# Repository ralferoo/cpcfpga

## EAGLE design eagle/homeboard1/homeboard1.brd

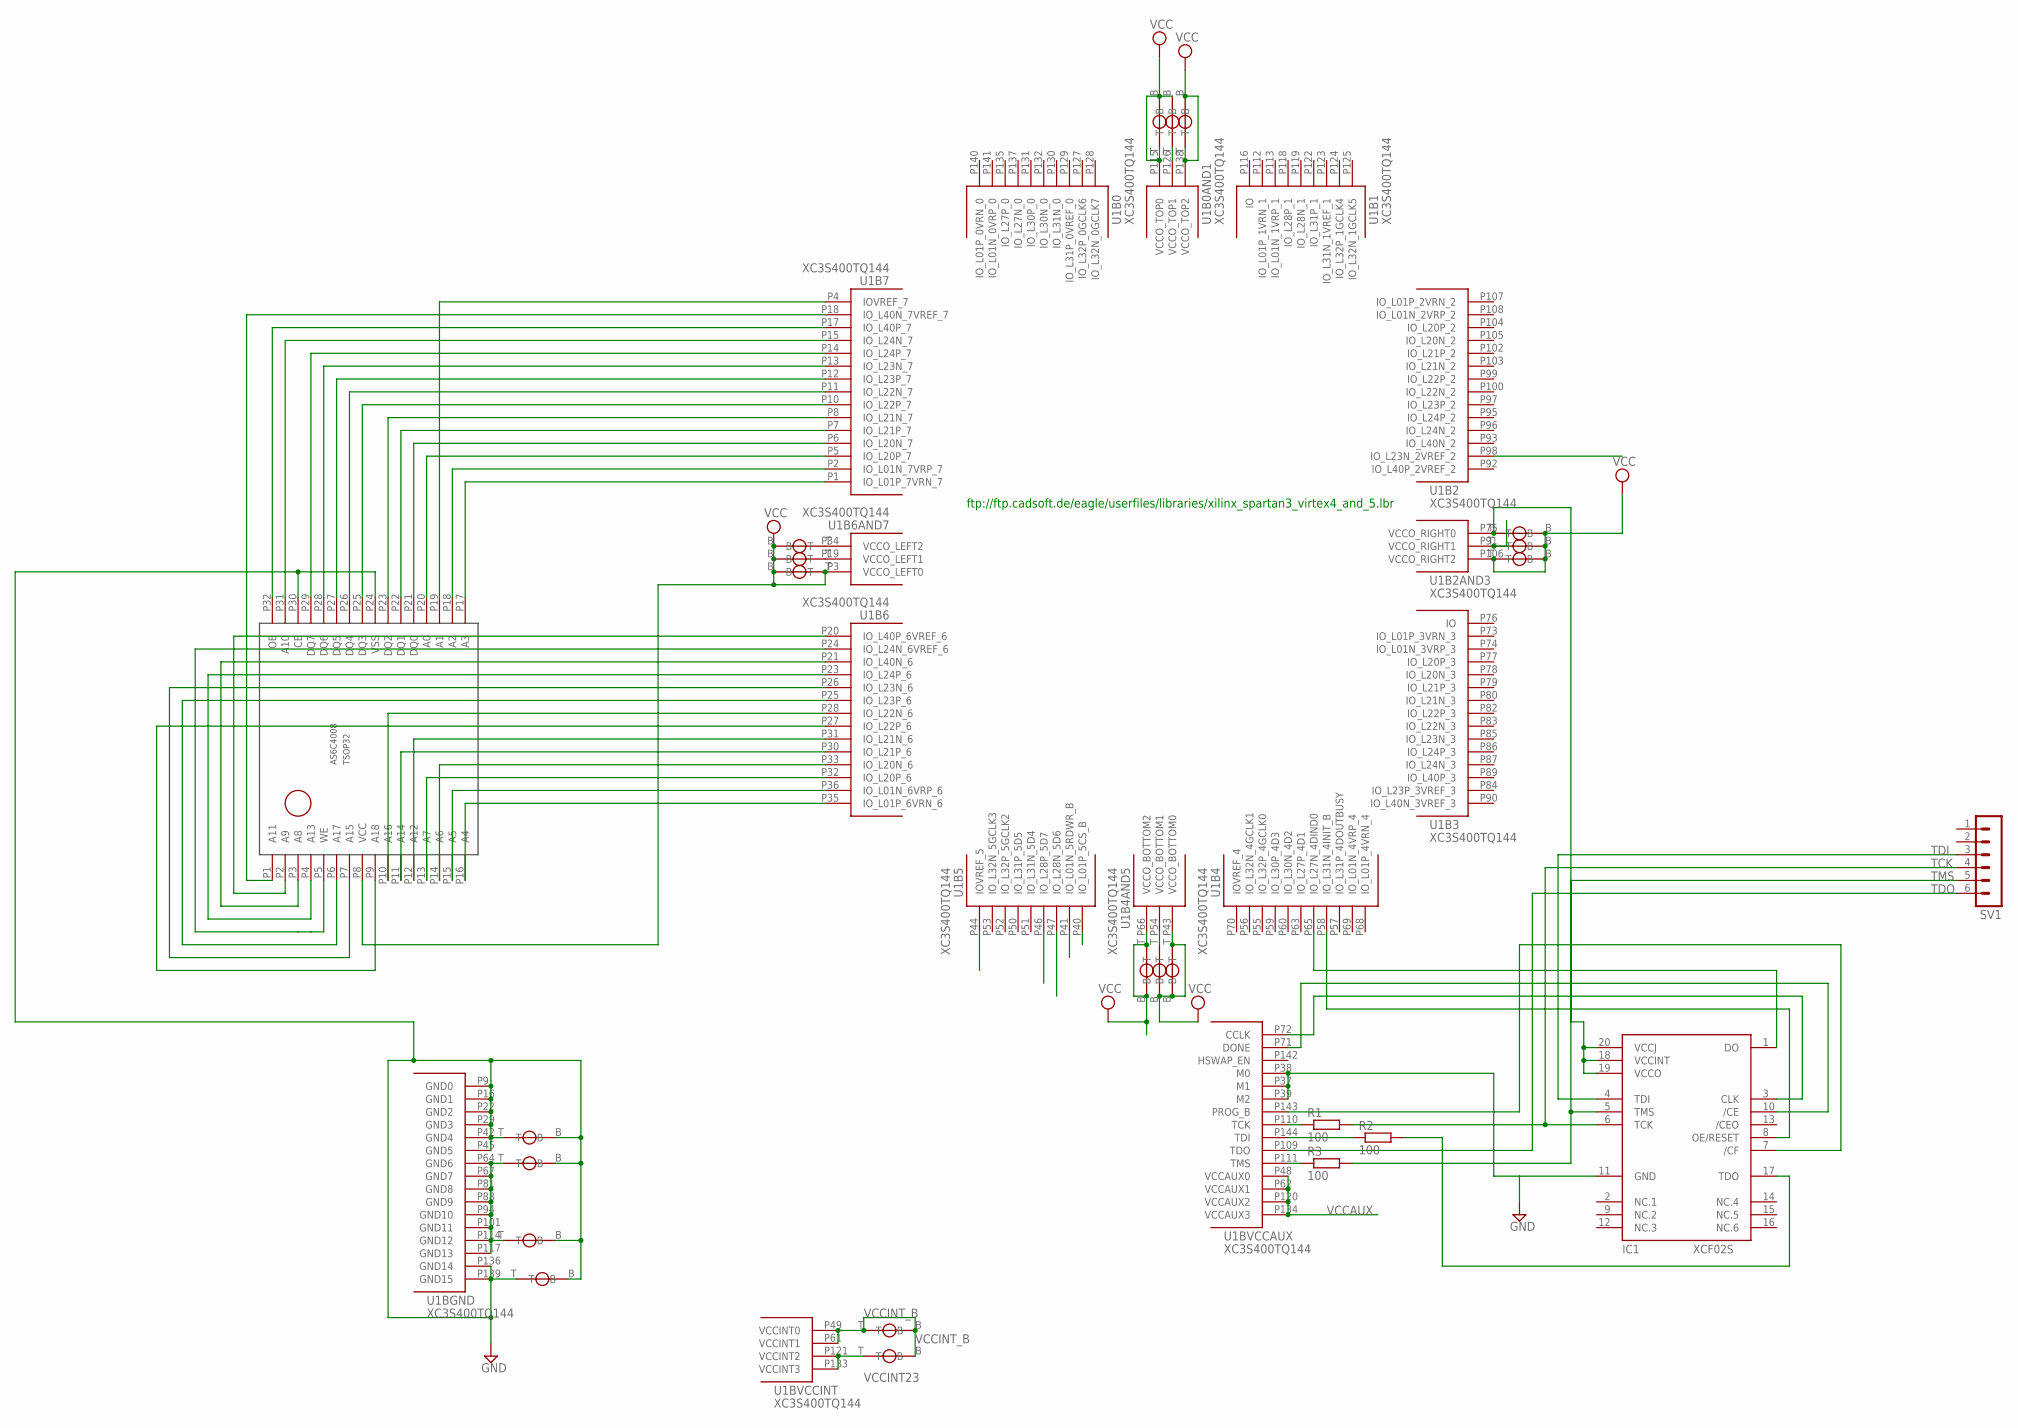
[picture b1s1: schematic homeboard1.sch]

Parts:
IC1: XCF02S; VO20
R1, R2, R3: 100; R0805
SV1: MA06-1
U1: XC3S400TQ144; TQ144
U$1, U$2, U$3, U$5, U$6, U$7, U$10, U$14, U$15, U$18, U$19, U$20, U$23, U$25, U$26, U$27, U$28, U$29: VIA_DIY
U$4: AS6C4008; TSOP32

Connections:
GND: IC1.11 (GND), U1.P9 (GND0), U1.P16 (GND1), U1.P22 (GND2), U1.P29 (GND3), U1.P37 (M1), U1.P38 (M0), U1.P39 (M2), U1.P42 (GND4), U1.P45 (GND5), U1.P136 (GND14), U1.P139 (GND15), U$2.B, U$3.B, U$3.T, U$4.P24 (VSS), U$4.P30 (CE), U$5.B, U$5.T, U$20.B
unnamed: U1.P1 (IO_L01P_7VRN_7), U$4.P17 (A3)
unnamed: U1.P2 (IO_L01N_7VRP_7), U$4.P18 (A2)
unnamed: U1.P126 (VCCO_TOP1), U$10.T
unnamed: U1.P64 (GND6), U1.P67 (GND7), U1.P81 (GND8), U1.P88 (GND9), U1.P94 (GND10), U1.P101 (GND11), U1.P114 (GND12), U1.P117 (GND13), U$2.T, U$20.T
unnamed: U1.P12 (IO_L23P_7), U$4.P27 (DQ5)
unnamed: U1.P13 (IO_L23N_7), U$4.P28 (DQ6)
unnamed: U1.P6 (IO_L20N_7), U$4.P21 (DQ0)
unnamed: R1.1, U1.P110 (TCK)
unnamed: IC1.1 (DO), U1.P65 (IO_L27N_4DIND0)
unnamed: U1.P7 (IO_L21P_7), U$4.P22 (DQ1)
unnamed: U1.P8 (IO_L21N_7), U$4.P23 (DQ2)
unnamed: R2.1, U1.P144 (TDI)
unnamed: IC1.17 (TDO), R2.2
unnamed: U1.P34 (VCCO_LEFT2), U$14.T
unnamed: U1.P19 (VCCO_LEFT1), U$15.T
unnamed: R3.1, U1.P111 (TMS)
unnamed: IC1.7 (/CF), U1.P143 (PROG_B)
unnamed: IC1.8 (OE/RESET), U1.P58 (IO_L31N_4INIT_B)
unnamed: IC1.3 (CLK), U1.P72 (CCLK)
unnamed: IC1.10 (/CE), U1.P71 (DONE)
unnamed: U1.P10 (IO_L22P_7), U$4.P25 (DQ3)
unnamed: U1.P11 (IO_L22N_7), U$4.P26 (DQ4)
unnamed: U1.P14 (IO_L24P_7), U$4.P29 (DQ7)
unnamed: U1.P54 (VCCO_BOTTOM1), U$25.T
unnamed: IC1.18 (VCCINT), IC1.19 (VCCO), IC1.20 (VCCJ), U1.P75 (VCCO_RIGHT0), U$29.T
unnamed: U1.P15 (IO_L24N_7), U$4.P31 (A10)
unnamed: U1.P91 (VCCO_RIGHT1), U$28.T
unnamed: U1.P17 (IO_L40P_7), U$4.P32 (OE)
unnamed: U1.P28 (IO_L22N_6), U$4.P10 (A16)
unnamed: U1.P30 (IO_L21P_6), U$4.P11 (A14)
unnamed: U1.P31 (IO_L21N_6), U$4.P12 (A12)
unnamed: U1.P20 (IO_L40P_6VREF_6), U$4.P2 (A9)
unnamed: U1.P32 (IO_L20P_6), U$4.P13 (A7)
unnamed: U1.P33 (IO_L20N_6), U$4.P14 (A6)
unnamed: U1.P27 (IO_L22P_6), U$4.P9 (A18)
unnamed: U1.P35 (IO_L01P_6VRN_6), U$4.P16 (A4)
unnamed: U1.P36 (IO_L01N_6VRP_6), U$4.P15 (A5)
unnamed: U1.P5 (IO_L20P_7), U$4.P20 (A0)
unnamed: U1.P4 (IOVREF_7), U$4.P19 (A1)
unnamed: U1.P18 (IO_L40N_7VREF_7), U$4.P1 (A11)
unnamed: U1.P23 (IO_L24P_6), U$4.P4 (A13)
unnamed: U1.P21 (IO_L40N_6), U$4.P3 (A8)
unnamed: U1.P24 (IO_L24N_6VREF_6), U$4.P5 (WE)
unnamed: U1.P25 (IO_L23P_6), U$4.P6 (A17)
unnamed: U1.P26 (IO_L23N_6), U$4.P7 (A15)
TCK: IC1.6 (TCK), R1.2, SV1.4
TDI: IC1.4 (TDI), SV1.3
TDO: SV1.6, U1.P109 (TDO)
TMS: IC1.5 (TMS), R3.2, SV1.5
VCC: U1.P3 (VCCO_LEFT0), U1.P43 (VCCO_BOTTOM0), U1.P66 (VCCO_BOTTOM2), U1.P106 (VCCO_RIGHT2), U1.P115 (VCCO_TOP0), U1.P138 (VCCO_TOP2), U$4.P8 (VCC), U$6.B, U$6.T, U$7.B, U$7.T, U$10.B, U$14.B, U$15.B, U$18.B, U$18.T, U$19.B, U$19.T, U$25.B, U$26.B, U$26.T, U$27.B, U$27.T, U$28.B, U$29.B
VCCAUX: U1.P48 (VCCAUX0), U1.P62 (VCCAUX1), U1.P120 (VCCAUX2), U1.P134 (VCCAUX3)
VCCINT23: U1.P121 (VCCINT2), U1.P133 (VCCINT3), U$23.T
VCCINT_B: U1.P49 (VCCINT0), U1.P61 (VCCINT1), U$1.B, U$1.T, U$23.B

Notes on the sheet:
ftp://ftp.cadsoft.de/eagle/userfiles/libraries/xilinx_spartan3_virtex4_and_5.lbr

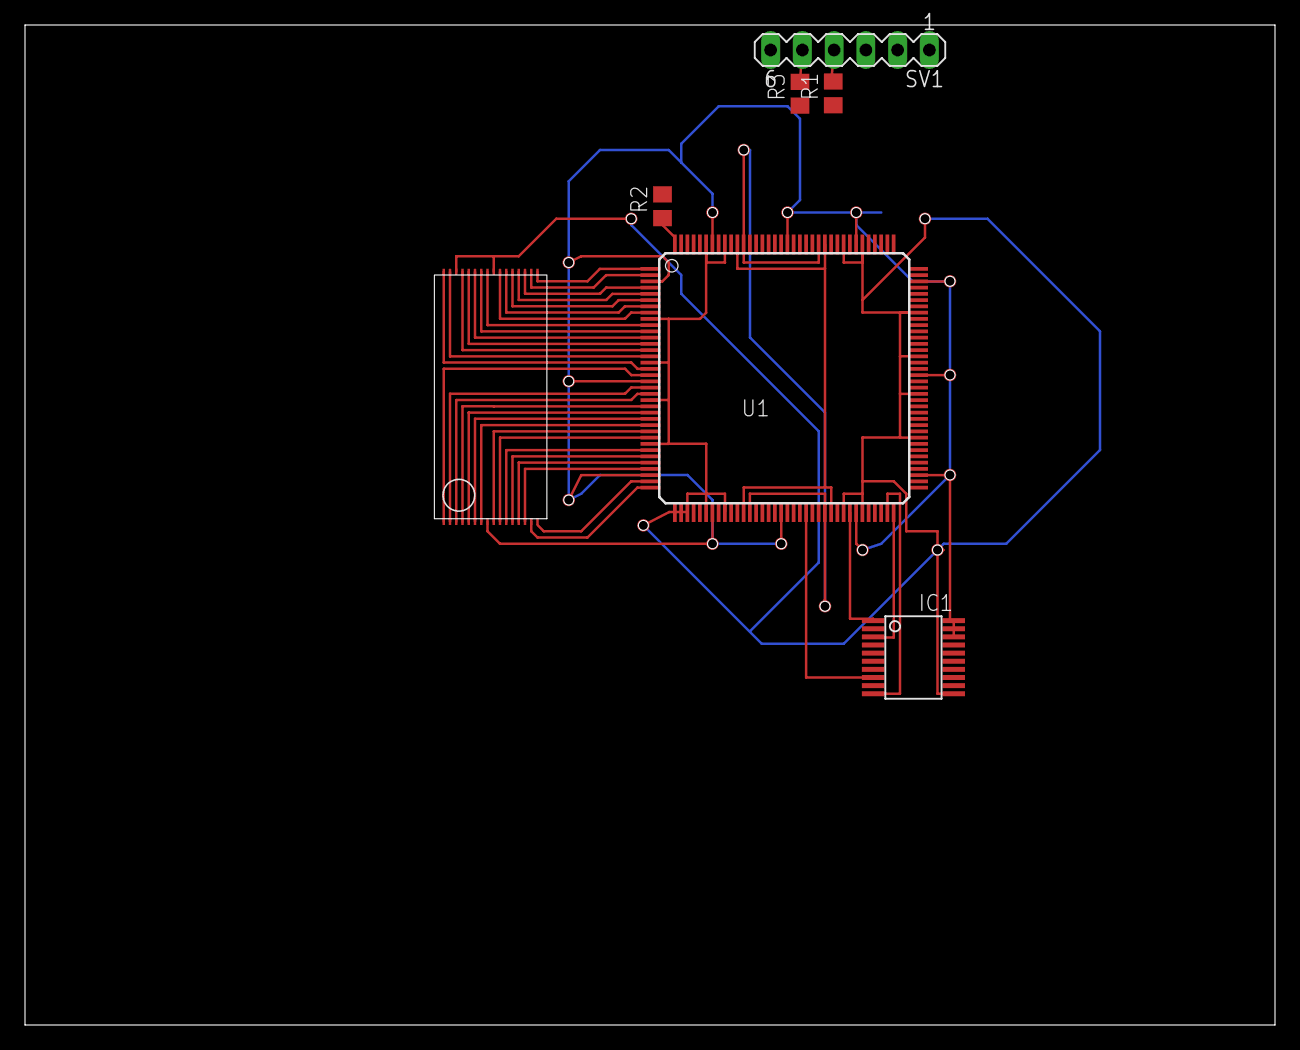
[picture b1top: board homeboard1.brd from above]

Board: 2 copper layers, 100.0 x 80.0 mm, 25 parts (0 on the bottom side), 54 nets.

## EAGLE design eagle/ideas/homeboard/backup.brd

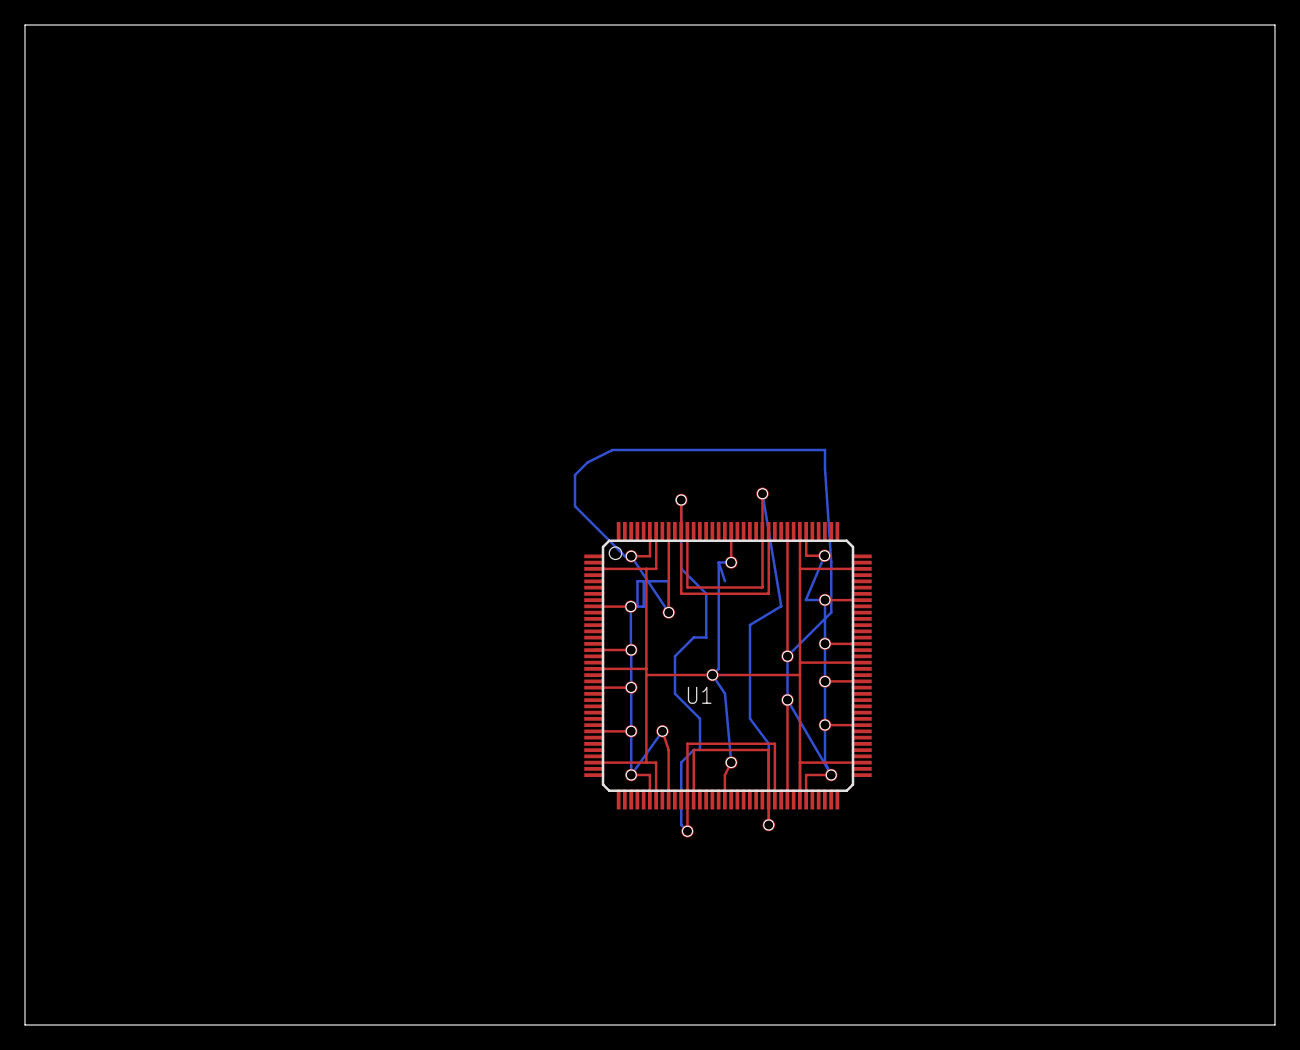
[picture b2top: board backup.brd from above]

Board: 2 copper layers, 100.0 x 80.0 mm, 24 parts (0 on the bottom side), 27 nets.

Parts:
U1: XC3S400TQ144; TQ144
U$1, U$2, U$4, U$5, U$6, U$7, U$8, U$9, U$10, U$11, U$12, U$13, U$14, U$15, U$16, U$17, U$18, U$19, U$20, U$21, U$22, U$23, U$24: VIA_DIY

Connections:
GND: U1.P139, U$20.T
GND_B: U$5.B, U$6.B, U$7.B, U$8.B, U$9.B, U$10.B, U$11.B, U$12.B, U$13.B, U$14.B, U$15.B, U$16.B, U$17.B, U$18.B, U$19.B, U$20.B
unnamed: U1.P9, U$5.T
unnamed: U1.P16, U$6.T
unnamed: U1.P22, U$7.T
unnamed: U1.P29, U$8.T
unnamed: U1.P42, U$9.T
unnamed: U1.P45, U$10.T
unnamed: U1.P64, U$11.T
unnamed: U1.P67, U$12.T
unnamed: U1.P81, U$13.T
unnamed: U1.P88, U$14.T
unnamed: U1.P94, U$15.T
unnamed: U1.P101, U$16.T
unnamed: U1.P114, U$17.T
unnamed: U1.P117, U$18.T
unnamed: U1.P136, U$19.T
unnamed: U1.P48, U1.P62, U$22.T
unnamed: U$21.B, U$23.B, U$24.B
unnamed: U1.P126, U$23.T
unnamed: U1.P54, U$21.T
unnamed: U$4.B, U$22.B
VCC: U1.P3, U1.P19, U1.P34, U1.P43, U1.P66, U1.P75, U1.P91, U1.P106, U1.P115, U1.P138, U$24.T
VCCAUX: U1.P120, U1.P134, U$4.T
VCCINT01: U1.P49, U1.P61, U$1.T
VCCINT23: U1.P121, U1.P133, U$2.T
VCCINT_B: U$1.B, U$2.B

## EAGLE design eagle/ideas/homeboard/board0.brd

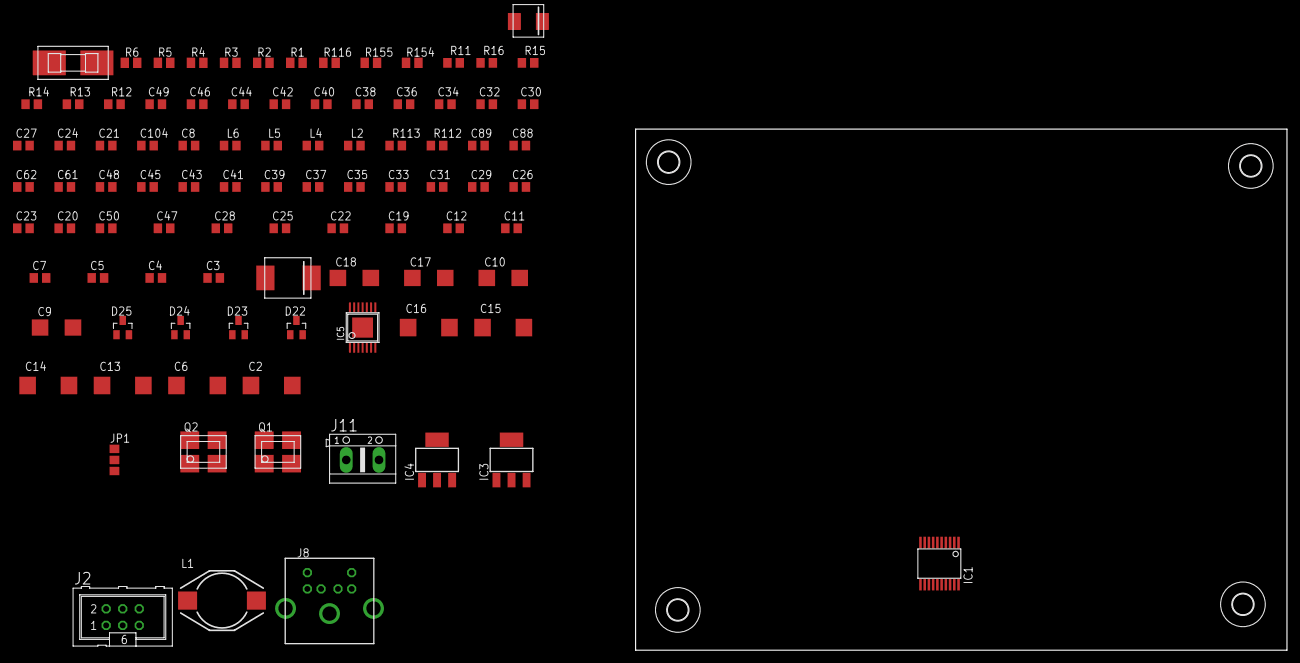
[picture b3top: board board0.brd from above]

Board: 2 copper layers, 100.0 x 80.0 mm, 98 parts (1 on the bottom side), 35 nets, no tracks yet.

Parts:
C2, C6, C13, C14, C15, C16: 47uF/10V/D; D/7343-31R
C3, C4, C5, C7, C11, C12, C19, C22, C25, C28, C47, C50: 1uF/Ker; C0805
C8: 3.3nF; C0805
C9, C10, C17, C18: 22uF/16V/C; C/6032-28R
C20, C23, C26, C29, C31, C33, C35, C37, C39, C41, C43, C45, C48, C61, C62, C88, C89: 100nF; C0805
C21, C24, C27, C30, C32, C34, C36, C38, C40, C42, C44, C46, C49: 10nF; C0805
C104: 1uF; C0805
D20: MBRS340; DO214AB
D21: P6SMB68CA; DO214AA
D22, D23, D24, D25: BAT54C; SOT23
F1: 3A; HASF
H1, H2, H3, H4: MOUNT-HOLE3.2; 3,2
IC1: XCF02S; VO20
IC2: XC3S400TQ144; TQ144
IC3, IC4: LT1117-ADJ; SOT223
IC5: LM2853; ETSSOP14
J2: ML6
J8: PS2CONN; MINIDIN-6
J11: AK500/2
JP1: 0R-JUMPA; A0R-JMP
L1: 6.8uH; DO3316P
L2, L4, L5, L6: 10nH; 0805
Q1: 24.000MHz; XO91
Q2: 32.000MHz; XO91
R1, R2, R3: 100; M0805
R4, R5, R155: 4k7; M0805
R6, R116, R154: 2k2; M0805
R11, R12: 39; R0805
R13: 220; R0805
R14, R15, R16: 0; R0805
R112: 150; R0805
R113: 4k7; R0805

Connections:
3V3OUT: C13.+, C14.+, C15.+, C16.+, L1.2, R14.1, R112.2
5V_SREG: C9.+, C10.+, C11.1, C12.1, C62.1, IC5.1, IC5.2, IC5.6, IC5.7, L2.1, L6.1
+1V2: C39.1, C40.1, C41.1, C42.1, C43.1, C44.1, C45.1, C46.1, C50.1, IC2.P49, IC2.P61, IC2.P121, IC2.P133, R16.2
+2V5: C3.1, C31.1, C32.1, C33.1, C34.1, C35.1, C36.1, C37.1, C38.1, IC2.P48, IC2.P62, IC2.P120, IC2.P134, R4.1, R6.1, R15.2
+3V3: C19.1, C20.1, C21.1, C22.1, C23.1, C24.1, C25.1, C26.1, C27.1, C28.1, C29.1, C30.1, C47.1, C48.1, C49.1, IC1.18, IC1.19, IC1.20, IC2.P3, IC2.P19, IC2.P34, IC2.P43, IC2.P54, IC2.P66, IC2.P75, IC2.P91, IC2.P106, IC2.P115, IC2.P126, IC2.P138, L4.2, L5.2, R5.2, R14.2, R154.2, R155.2
+5V: C5.1, C17.+, C18.+, C61.1, D20.K, D21.K, D25.1, D25.2, F1.1, IC3.3, L2.2, L6.2, R116.2
CLK: IC2.P52, JP1.2
FPGA_DIN: IC1.1, IC2.P65
FPGA_INITB: IC1.8, IC2.P58, R5.1
GND: C2.-, C3.2, C4.2, C5.2, C6.-, C7.2, C8.2, C9.-, C10.-, C11.2, C12.2, C13.-, C14.-, C15.-, C16.-, C17.-, C18.-, C19.2, C20.2, C21.2, C22.2, C23.2, C24.2, C25.2, C26.2, C27.2, C28.2, C29.2, C30.2, C31.2, C32.2, C33.2, C34.2, C35.2, C36.2, C37.2, C38.2, C39.2, C40.2, C41.2, C42.2, C43.2, C44.2, C45.2, C46.2, C47.2, C48.2, C49.2, C50.2, C61.2, C62.2, C88.2, C89.2, C104.2, D20.A, D21.A, IC1.11, IC2.P9, IC2.P16, IC2.P22, IC2.P29, IC2.P37, IC2.P38, IC2.P39, IC2.P42, IC2.P45, IC2.P64, IC2.P67, IC2.P81, IC2.P88, IC2.P94, IC2.P101, IC2.P114, IC2.P117, IC2.P136, IC2.P139, IC2.P142, IC4.1, IC5.3, IC5.10, IC5.11, IC5.15, J2.3, J8.SHIELD.1, J8.SHIELD.2, J8.SHIELD.3, J11.1, Q1.2, Q2.2, R11.1, R13.1, R113.1
unnamed: IC1.3, IC2.P72, R155.1
unnamed: IC1.10, IC2.P71, R6.2
unnamed: IC2.P111, R1.1
unnamed: IC2.P110, R2.1
unnamed: C7.1, IC3.1, R11.2, R12.1
unnamed: IC1.17, R3.2
unnamed: IC2.P144, R3.1
unnamed: D22.1, D22.2, IC1.7, IC2.P143, R4.2
unnamed: IC5.8, IC5.9, L1.1
unnamed: C8.1, IC5.4
unnamed: C6.+, IC4.2, IC4.4, R13.2, R16.1
unnamed: C104.1, D25.3, J2.1
unnamed: C2.+, C4.1, IC3.2, IC3.4, IC4.3, R12.2, R15.1
unnamed: JP1.1, Q2.3
unnamed: JP1.3, Q1.3
unnamed: IC5.14, R112.1, R113.2
unnamed: F1.2, J11.2
unnamed: D23.3, D24.1
Q1_3V3: C88.1, L4.1, Q1.1, Q1.4
Q2_3V3: C89.1, L5.1, Q2.1, Q2.4
TCK: IC1.6, J2.5, R2.2
TDI: IC1.4, J2.4
TDO: D24.3, IC2.P109, R154.1
TDO_JTAG: D23.1, J2.6, R116.1
TMS: IC1.5, J2.2, R1.2

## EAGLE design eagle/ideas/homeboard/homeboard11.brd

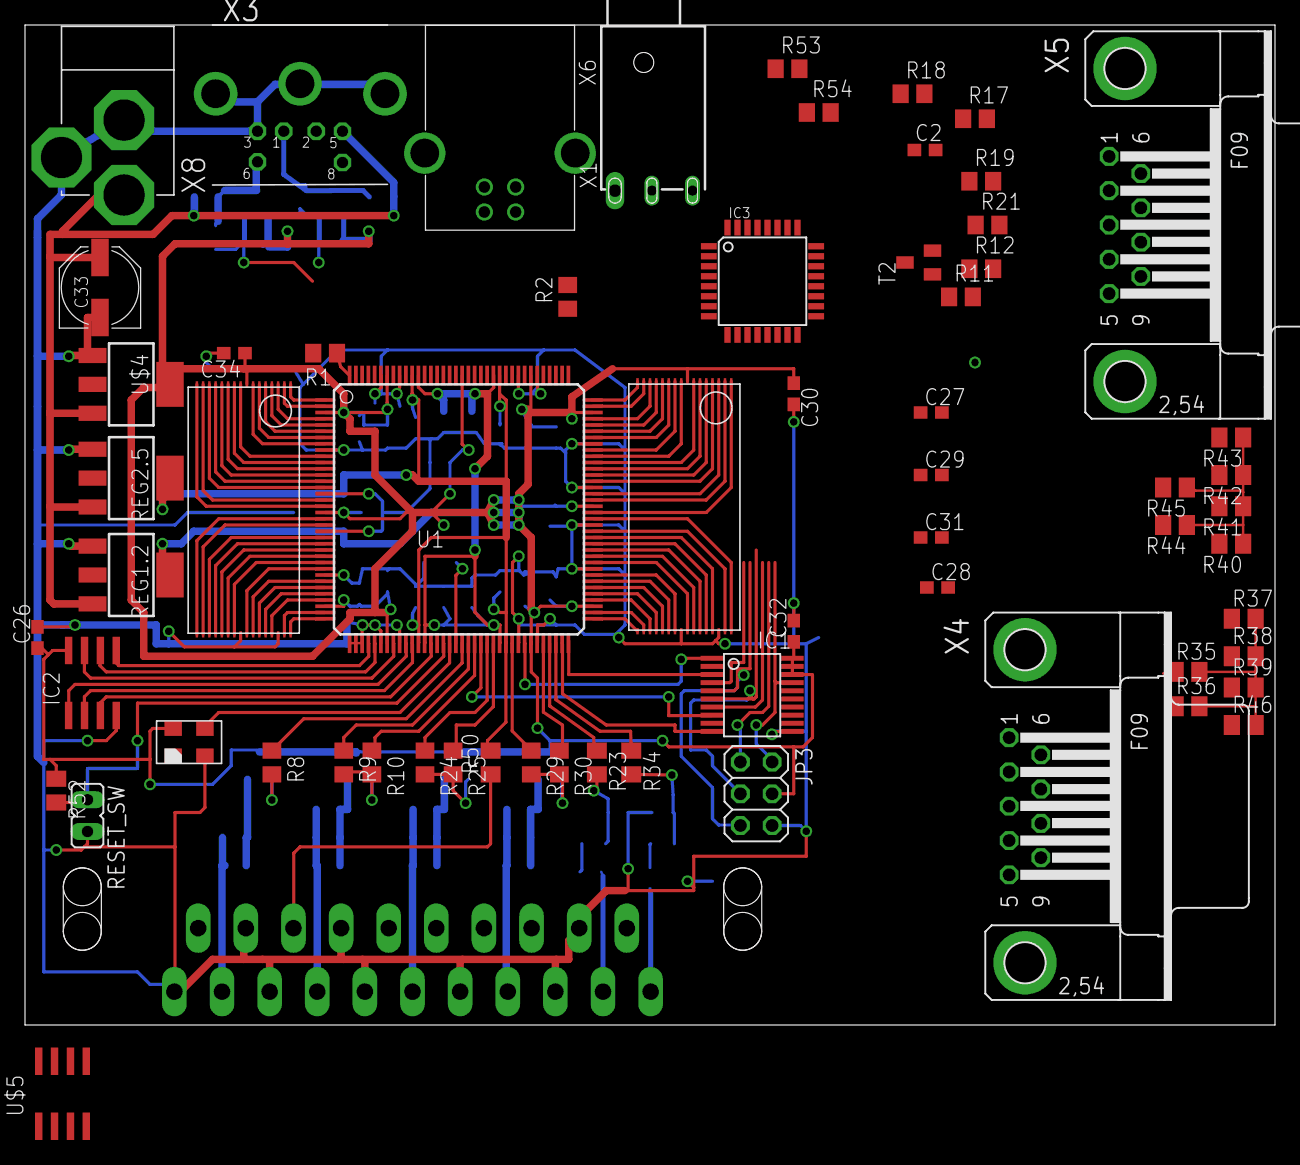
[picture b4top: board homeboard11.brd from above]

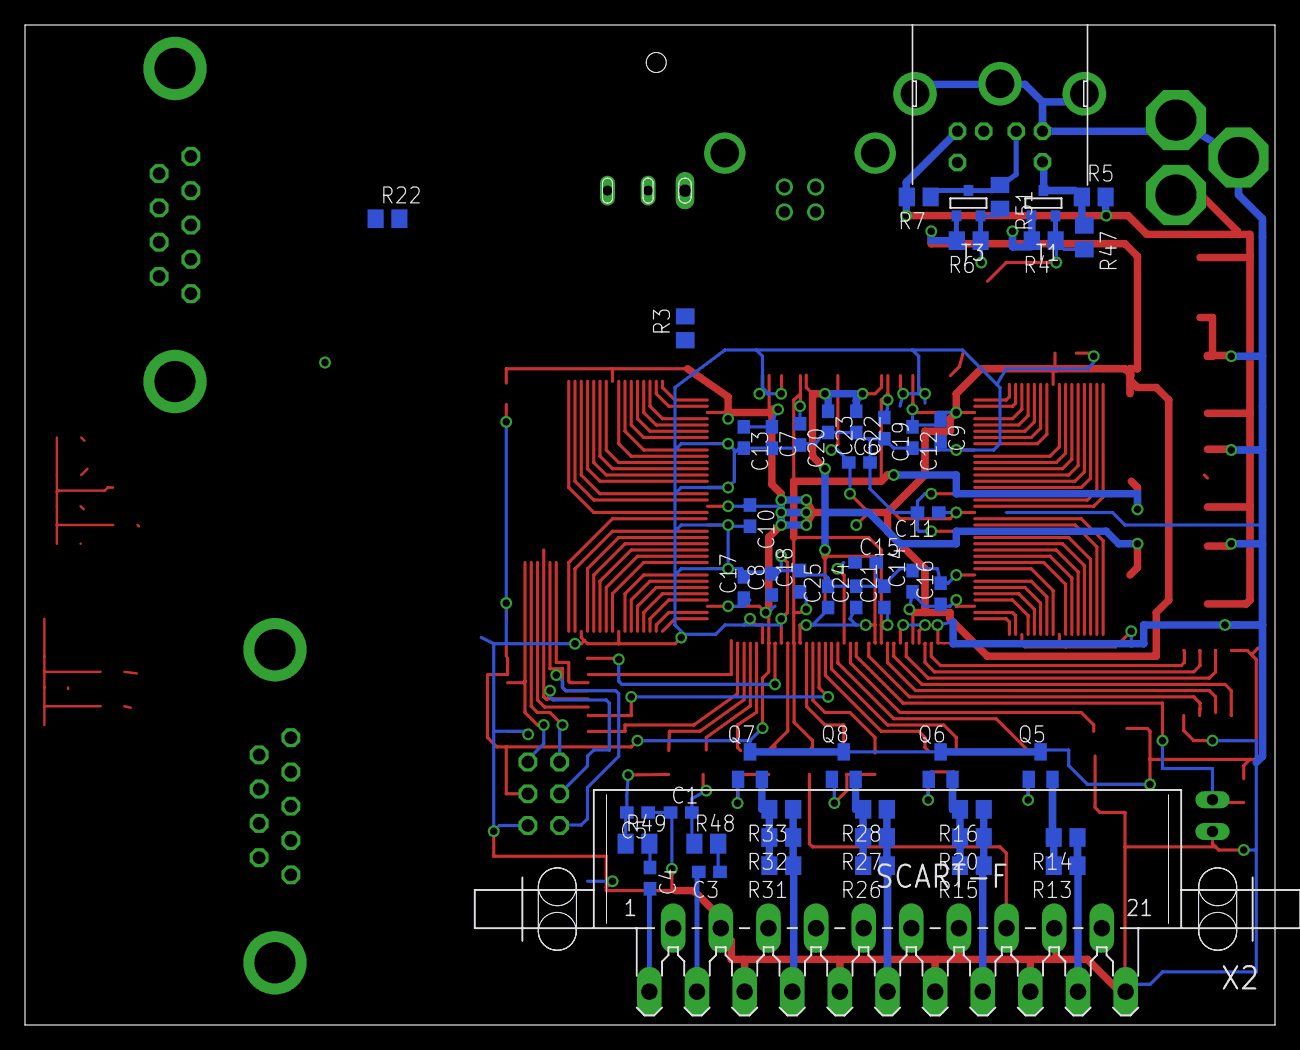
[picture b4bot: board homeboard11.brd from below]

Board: 2 copper layers, 100.0 x 80.0 mm, 115 parts (52 on the bottom side), 139 nets.

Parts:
C1, C3, C4, C5: C0603
C2, C6, C7, C8, C9, C10, C11, C12, C13, C14, C15, C16, C17, C18, C19, C20, C21, C22, C23, C24, C25, C26, C27, C28, C29, C30, C31, C32, C34: 100nF; C0603
C33: 100u; PANASONIC_D
IC1: XCF02S; VO20
IC2: 25LC080SN; SO-08
IC3: ATMEGA32U2-TQFP; TQFP32-08
JP3: 2X03
Q5, Q6, Q7, Q8: BC848SMD; SOT23
R1, R2, R3: 100; R0805
R4, R5, R6, R7, R10, R22, R25, R30: 1000; R0805
R8, R9, R14, R24, R29: 2200; R0805
R11: 75; R0805
R12: 750; R0805
R13, R16, R27, R32: 680; R0805
R15, R26, R31, R47, R51: 270; R0805
R17, R19: 10000; R0805
R18, R20, R28, R33: 4700; R0805
R21: 47000; R0805
R23, R34, R35, R36, R37, R38, R39, R40, R41, R42, R43, R44, R45, R46, R48, R49: M0805
R50: 2k2; M0805
R52: 4K7; M0805
R53, R54: 22; R0805
REG1.2: 1.2V; SOT223
REG2.5: 2.5V; SOT223
RESET_SW: JP1
T1, T3: BSS138; SOT-23
T2: BC848; SOT23
U1: XC3S400TQ144; TQ144
U$1, U$6: AS6C4008; TSOP32
U$2: TXO_7C; OSC_7C
U$4: 3.3V; SOT223
U$5: MC33269D; SO8
X1: 1503_04
X2: SCART-F
X3: M_DIN6
X4, X5: F09HP
X6: MINI-USB_4P-85-32004-10X; 85-32004-10X
X8: DC21MMX; DC-21MM

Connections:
B0: R30.1, U1.P68
B1: R29.1, U1.P63
CASIN: R21.2, T2.2
CLK16: U1.P53, U$2.OUT
CLK_5V: R5.1, R47.1, T1.1, X3.6
CSYNC: R8.1, U1.P55
DATA_5V: R7.1, R51.1, T3.1, X3.1
D_FASTBLANKING: R11.1, R12.2
FL_DI: IC2.5, U1.P40
FL_DO: IC2.2, U1.P47
FL_HOLD: IC2.7, U1.P44
FL_SCLK: IC2.6, U1.P41
FL_SEL: IC2.1, U1.P46
FL_WP: IC2.3, U1.P50
FPGA_AUDIO_LEFT: R23.1, U1.P69
FPGA_AUDIO_RIGHT: R34.1, U1.P70
G0: R25.1, U1.P60
G1: R24.1, U1.P59
GND: C1.1, C5.1, C6.2, C7.2, C8.2, C9.2, C10.2, C11.2, C12.2, C13.2, C14.2, C15.2, C16.2, C17.2, C18.2, C19.2, C20.2, C21.2, C22.2, C23.2, C24.2, C25.2, C26.2, C27.2, C28.2, C29.2, C30.2, C31.2, C32.2, C33.-, C34.2, IC1.11, IC2.4, IC3.3, JP3.6, R12.1, R17.1, R19.1, R21.1, REG1.2.1, REG2.5.1, RESET_SW.2, U1.P9, U1.P16, U1.P22, U1.P29, U1.P37, U1.P38, U1.P39, U1.P42, U1.P45, U1.P64, U1.P67, U1.P81, U1.P88, U1.P94, U1.P101, U1.P114, U1.P117, U1.P136, U1.P139, U$1.P24, U$1.P30, U$2.GND, U$4.1, U$6.P24, U$6.P30, X1.3, X2.4, X2.5, X2.9, X2.13, X2.14, X2.17, X2.18, X2.21, X3.3, X3.SH1, X3.SH2, X3.SH3, X4.8, X4.G1, X5.8, X5.G1, X8.1, X8.3
unnamed: U1.P108, U$1.P16
unnamed: U1.P107, U$1.P15
unnamed: U1.P105, U$1.P14
unnamed: U1.P104, U$1.P13
unnamed: U1.P103, U$1.P12
unnamed: U1.P102, U$1.P11
unnamed: U1.P100, U$1.P10
unnamed: U1.P99, U$1.P9
unnamed: U1.P98, U$1.P7
unnamed: U1.P97, U$1.P6
unnamed: U1.P96, U$1.P5
unnamed: U1.P95, U$1.P4
unnamed: U1.P93, U$1.P3
unnamed: U1.P92, U$1.P2
unnamed: U1.P90, U$1.P1
unnamed: U1.P73, U$1.P17
unnamed: U1.P74, U$1.P18
unnamed: U1.P76, U$1.P19
unnamed: U1.P77, U$1.P20
unnamed: U1.P78, U$1.P21
unnamed: U1.P79, U$1.P22
unnamed: U1.P80, U$1.P23
unnamed: U1.P82, U$1.P25
unnamed: U1.P83, U$1.P26
unnamed: U1.P84, U$1.P27
unnamed: U1.P85, U$1.P28
unnamed: U1.P86, U$1.P29
unnamed: U1.P87, U$1.P31
unnamed: U1.P89, U$1.P32
unnamed: R35.1, X5.7
unnamed: R36.1, X5.6
unnamed: R37.1, X5.4
unnamed: R38.1, X5.3
unnamed: R39.1, X5.2
unnamed: IC1.3, U1.P72
unnamed: R53.1, X6.2
unnamed: R46.1, X5.1
unnamed: IC1.10, U1.P71
unnamed: R2.1, U1.P110
unnamed: IC1.7, U1.P143
unnamed: R40.2, X4.1
unnamed: R1.1, U1.P144
unnamed: R3.1, U1.P111
unnamed: R41.2, X4.2
unnamed: R42.2, X4.3
unnamed: R43.2, X4.4
unnamed: R44.2, X4.6
unnamed: R45.2, X4.7
unnamed: IC3.29, R54.2
unnamed: C1.2, R23.2, R48.1
unnamed: C3.1, R48.2
unnamed: Q6.1, R9.2, R10.2
unnamed: Q6.2, R15.2, R16.2, R20.2
unnamed: Q8.1, R24.2, R25.2
unnamed: Q8.2, R26.2, R27.2, R28.2
unnamed: Q7.1, R29.2, R30.2
unnamed: Q7.2, R31.2, R32.2, R33.2
unnamed: Q5.2, R13.2, R14.2
unnamed: C2.2, R18.1, R19.2, T2.1
unnamed: C2.1, R17.2, X1.1
unnamed: R18.2, R22.2
unnamed: Q5.1, R8.2
unnamed: C4.1, R49.2
unnamed: C5.2, R34.2, R49.1
unnamed: R54.1, X6.3
unnamed: U1.P1, U$6.P1
unnamed: IC3.30, R53.2
unnamed: IC3.28, X6.4
unnamed: U1.P2, U$6.P2
unnamed: U1.P4, U$6.P3
unnamed: U1.P5, U$6.P4
unnamed: U1.P6, U$6.P5
unnamed: U1.P7, U$6.P6
unnamed: U1.P8, U$6.P7
unnamed: U1.P10, U$6.P9
unnamed: U1.P11, U$6.P10
unnamed: U1.P12, U$6.P11
unnamed: U1.P13, U$6.P12
unnamed: U1.P14, U$6.P13
unnamed: U1.P15, U$6.P14
unnamed: U1.P17, U$6.P15
unnamed: U1.P18, U$6.P16
unnamed: U1.P20, U$6.P17
unnamed: U1.P21, U$6.P18
unnamed: U1.P23, U$6.P19
unnamed: U1.P24, U$6.P20
unnamed: U1.P25, U$6.P21
unnamed: U1.P26, U$6.P22
unnamed: U1.P27, U$6.P23
unnamed: U1.P28, U$6.P25
unnamed: U1.P30, U$6.P26
unnamed: U1.P31, U$6.P27
unnamed: U1.P32, U$6.P28
unnamed: U1.P33, U$6.P29
unnamed: U1.P35, U$6.P31
unnamed: U1.P36, U$6.P32
PROM_DO: IC1.1, U1.P65
PROM_INITB: IC1.8, U1.P58
PS2CLK: R4.1, R47.2, T1.2, U1.P141
PS2DAT: R6.1, R51.2, T3.2, U1.P140
R0: R10.1, U1.P57
R1: R9.1, U1.P56
RESET: R52.2, RESET_SW.1, U1.P52
SCART_BLANKING: R50.1, X2.16
SCART_BLUE: R31.1, R32.1, R33.1, X2.7
SCART_COMP: R13.1, R14.1, X2.19
SCART_GREEN: R26.1, R27.1, R28.1, X2.11
SCART_LEFT: C3.2, X2.3
SCART_RED: R15.1, R16.1, R20.1, X2.15
SCART_RIGHT: C4.2, X2.1
TCK: IC1.6, IC3.18, JP3.3, R2.2
TDI_FPGA: IC3.20, R1.2
TDO_EXP: IC3.21, JP3.1
TDO_FPGA: IC1.4, U1.P109
TDO_PROM: IC1.17, IC3.22, JP3.2
TMS: IC1.5, IC3.19, JP3.5, R3.2
VCC: C6.1, C7.1, C8.1, C9.1, C10.1, C11.1, C12.1, C13.1, C14.1, C15.1, C16.1, C17.1, C26.1, C27.1, C28.1, C29.1, C30.1, C31.1, C32.1, C34.1, IC1.18, IC1.19, IC1.20, IC2.8, IC3.4, IC3.31, IC3.32, JP3.4, Q5.3, Q6.3, Q7.3, Q8.3, R4.2, R6.2, R22.1, R35.2, R36.2, R37.2, R38.2, R39.2, R40.1, R41.1, R42.1, R43.1, R44.1, R45.1, R46.2, R52.1, T1.3, T2.3, T3.3, U1.P3, U1.P19, U1.P34, U1.P43, U1.P54, U1.P66, U1.P75, U1.P91, U1.P106, U1.P115, U1.P126, U1.P138, U$1.P8, U$2.VDD, U$4.4, U$6.P8
VCC5: C33.+, R5.2, R7.2, REG1.2.3, REG2.5.3, U$4.3, X3.5, X8.2
VCCAUX: C18.1, C19.1, C20.1, C21.1, R50.2, REG2.5.4, U1.P48, U1.P62, U1.P120, U1.P134
VCCINT: C22.1, C23.1, C24.1, C25.1, REG1.2.4, U1.P49, U1.P61, U1.P121, U1.P133
